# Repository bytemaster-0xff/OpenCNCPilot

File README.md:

# DIY PCB Fab

NOTE: Work in proces, mostly usable but use at your own risk and download updates often.

####Suite of tools for the PCB DIY'er who uses a CNC and/or Laser Cutter to Create Home Brew PCBs

DIY PCB Fab was based off and inspired by the highly successful OpenCNCPilot project by @martin

Key Features

* Open Eagle BRD Files and Generate GCode for Drill and Cutout Milling
* Visualization of Eagle BRD Files 

  [DOCUMENTATION IN PROCESS]

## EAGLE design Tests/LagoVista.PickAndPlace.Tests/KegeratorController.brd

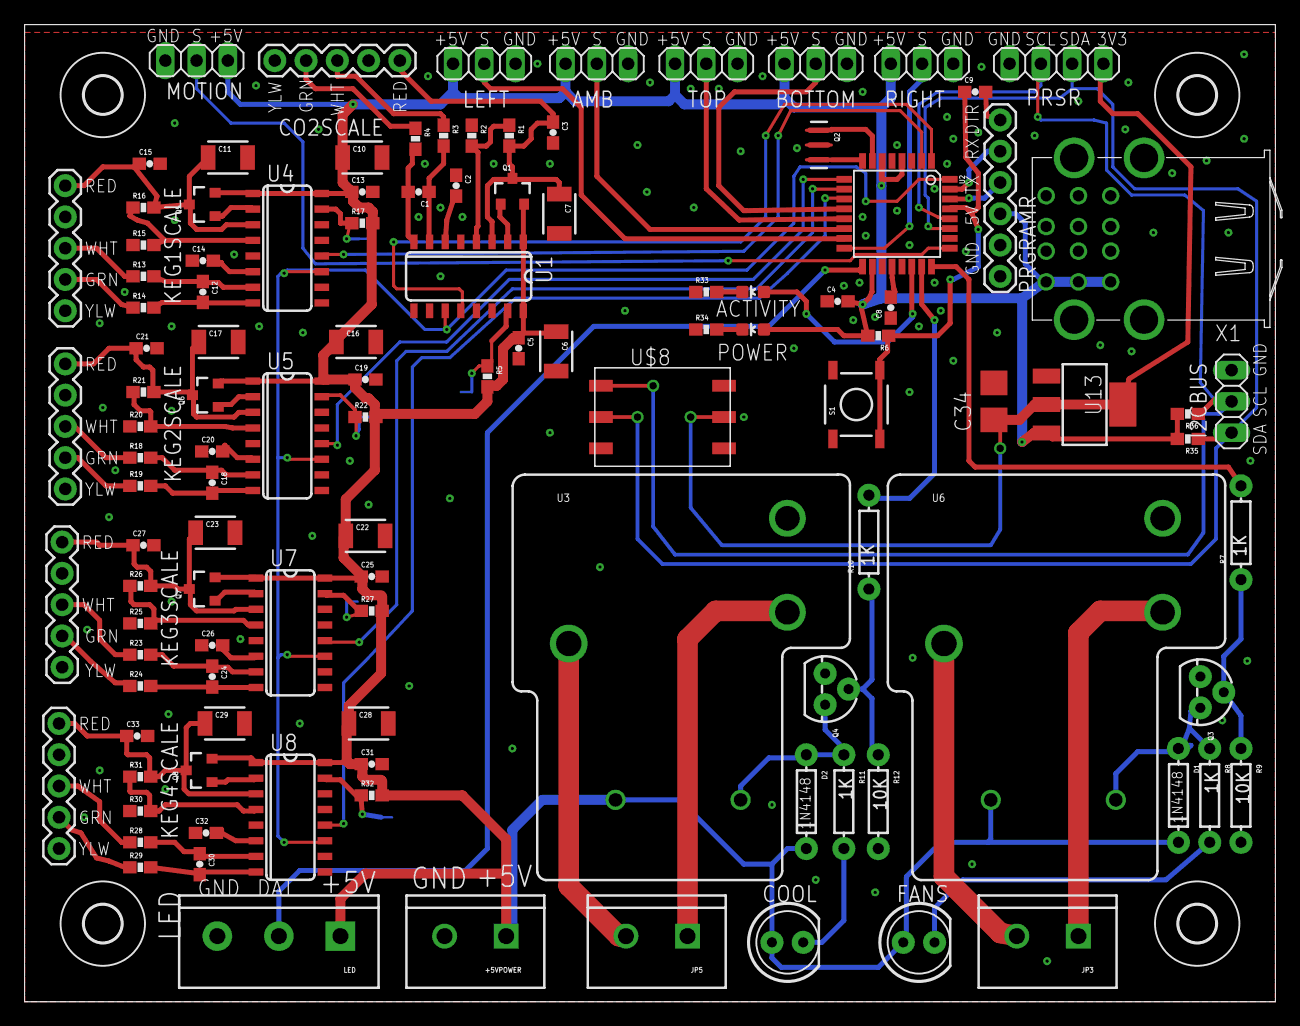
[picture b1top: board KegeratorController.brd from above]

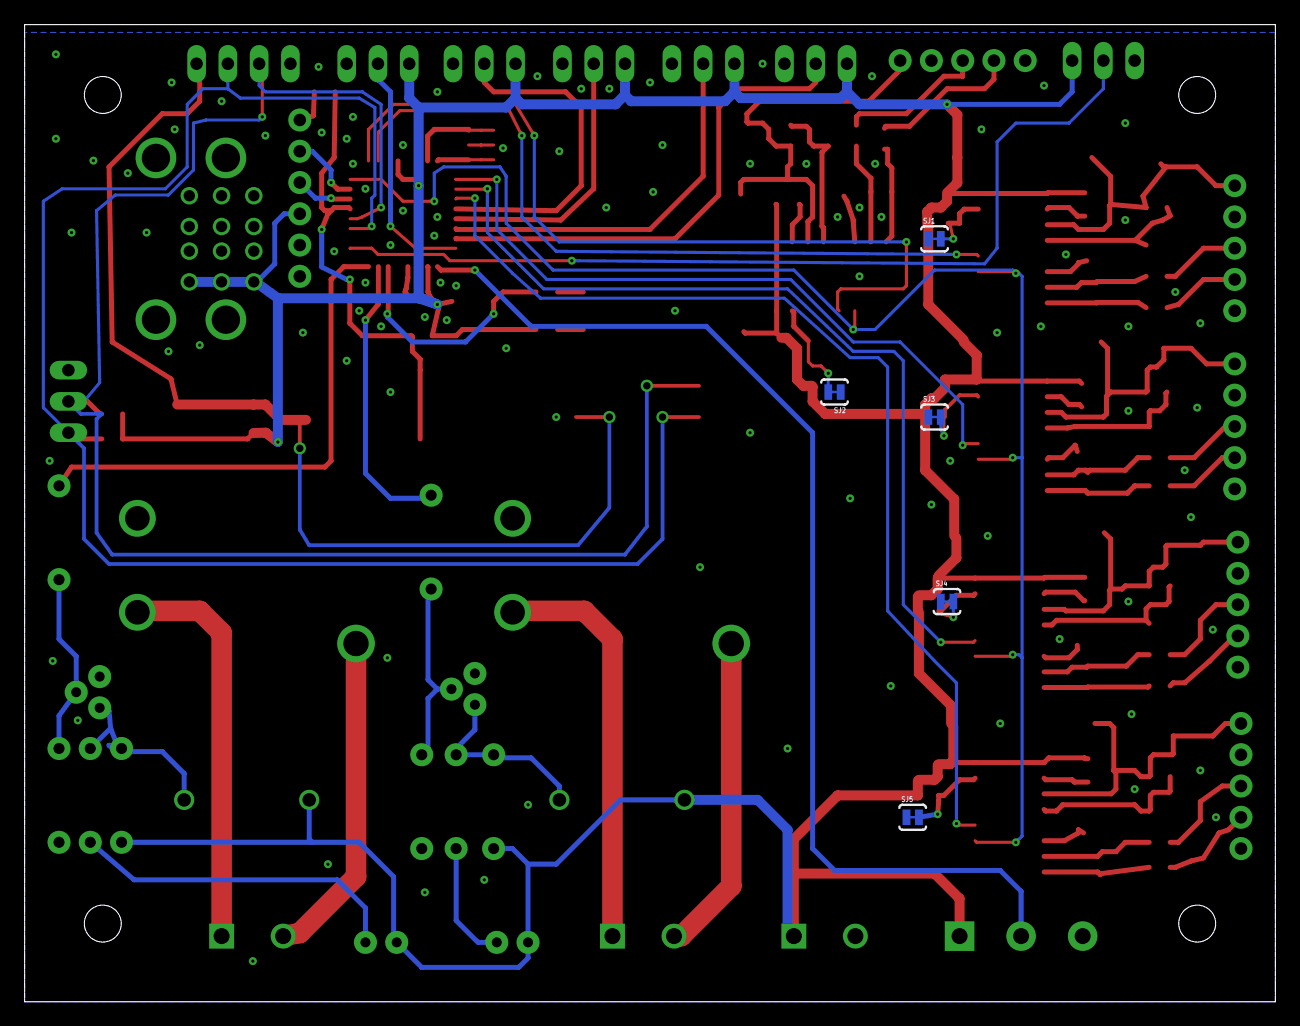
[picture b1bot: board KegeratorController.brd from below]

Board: 2 copper layers, 101.6 x 79.4 mm, 123 parts (5 on the bottom side), 85 nets.

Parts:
+5VPOWER: Load; SCREWTERMINAL-5MM-2
ACTIVITY: Red; 0603-LED-ALT1
AMB: 1X03
BOTTOM: 1X03
C1, C2, C3, C4, C5, C8, C9, C12, C13, C14, C15, C18, C19, C20, C21, C24, C25, C26, C27, C30, C31, C32, C33: 0.1uF; 0603-CAP
C6, C7, C10, C11, C16, C17, C22, C23, C28, C29: 10uF; 1210
C34: 10uF; CT3528
CO2SCALE: 1X05
COOL: LED5MM
D1, D2: 1N4148; DIODE-1N4148
FANS: LED5MM
I2CBUS: 1X03
JP3, JP5: Load; SCREWTERMINAL-5MM-2
KEG1SCALE, KEG2SCALE, KEG3SCALE, KEG4SCALE: 1X05
LED: SCREWTERMINAL-5MM-3
LEFT: 1X03
MOTION: 1X03
POWER: Red; 0603-LED-ALT1
PRGRAMR: FTDI Basic; 1X06
PRSR: 1X04
Q1, Q5, Q6, Q7, Q8: MMBT4403; SOT23-3
Q2: 8/16/20MHz; RESONATOR-SMD-1:1
Q3, Q4: 2N3904; TO-92
R1, R16, R21, R26, R31: 20K; 0603-RES
R2, R15, R20, R25, R30: 8.2K; 0603-RES
R3, R4, R13, R14, R18, R19, R23, R24, R28, R29: 100; 0603-RES
R5, R6, R17, R22, R27, R32, R35, R36: 10K; 0603-RES
R7, R8, R10, R11: 1K; AXIAL-0.3
R9, R12: 10K; AXIAL-0.3
R33, R34: 1K; 0603-RES
RIGHT: 1X03
S1: Reset; TACTILE-SWITCH-SMD-ALT01
SJ1, SJ2, SJ3, SJ4, SJ5: PAD-JUMPER-2-NC_BY_TRACE_YES_SILK
TOP: 1X03
U1, U4, U5, U7, U8: HX711; SO16
U2: ATMEGA328; TQFP32-08
U3, U6: RELAYPTH3; RELAY-T9A-2
U13: LM1117MP-3.3; SOT223
U$4, U$5, U$6, U$7: 3,0
U$8: ABPMANN030PG2A3; SMTAN
X1: USB_3P-85-32003-00X-1; 85-32003-00X-1

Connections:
+3V3: C34.+, PRSR.1, U13.2, U13.4, U$8.P$2
A2+: KEG1SCALE.2, R14.1
A2-: KEG1SCALE.3, R13.1
A3+: KEG2SCALE.2, R19.1
A3-: KEG2SCALE.3, R18.1
A4+: KEG3SCALE.2, R24.1
A4-: KEG3SCALE.3, R23.1
A5+: KEG4SCALE.2, R29.1
A5-: KEG4SCALE.3, R28.1
A+: CO2SCALE.2, R4.1
A-: CO2SCALE.3, R3.1
AREF: C8.2, U2.20
AVDD: C3.1, C7.1, CO2SCALE.5, Q1.3, R1.2, U1.3
AVDD2: C11.1, C15.1, KEG1SCALE.5, Q5.3, R16.2, U4.3
AVDD3: C17.1, C21.1, KEG2SCALE.5, Q6.3, R21.2, U5.3
AVDD4: C23.1, C27.1, KEG3SCALE.5, Q7.3, R26.2, U7.3
AVDD5: C29.1, C33.1, KEG4SCALE.5, Q8.3, R31.2, U8.3
COIL1: D2.A, Q4.3, R11.P$1, U3.COIL2
COIL2: D1.A, Q3.3, R8.P$1, U6.COIL2
COMPRESSOR_RELAY: R10.P$2, U2.23
DAT1: U1.12, U2.1
DAT2: U2.2, U4.12
DAT3: U2.9, U5.12
DAT4: U2.10, U7.12
DAT5: U2.11, U8.12
DHT11-1: LEFT.2, U2.15
DHT11-2: RIGHT.2, U2.16
DHT22-1: BOTTOM.2, U2.12
DHT22-2: TOP.2, U2.13
DHT22-3: AMB.2, U2.14
DTR: C9.2, PRGRAMR.1
GND: +5VPOWER.2, AMB.3, BOTTOM.3, C2.1, C3.2, C4.1, C5.2, C6.2, C7.2, C8.1, C10.2, C11.2, C13.2, C14.1, C15.2, C16.2, C17.2, C19.2, C20.1, C21.2, C22.2, C23.2, C25.2, C26.1, C27.2, C28.2, C29.2, C31.2, C32.1, C33.2, C34.-, CO2SCALE.1, CO2SCALE.4, I2CBUS.3, KEG1SCALE.1, KEG1SCALE.4, KEG2SCALE.1, KEG2SCALE.4, KEG3SCALE.1, KEG3SCALE.4, KEG4SCALE.1, KEG4SCALE.4, LED.3, LEFT.3, MOTION.3, PRGRAMR.5, PRGRAMR.6, PRSR.4, Q2.2, Q3.1, Q4.1, R2.1, R9.P$2, R12.P$2, R15.1, R20.1, R25.1, R30.1, R33.1, R34.1, RIGHT.3, S1.1, S1.2, SJ1.1, SJ2.1, SJ3.1, SJ4.1, SJ5.1, TOP.3, U1.5, U1.14, U2.3, U2.5, U2.21, U4.5, U4.14, U5.5, U5.14, U7.5, U7.14, U8.5, U8.14, U13.1, U$8.P$1, X1.1-4, X1.2-4, X1.3-4
HEAD_FAN_RELAY: R7.P$2, U2.24
I2C-SCL: I2CBUS.2, PRSR.3, R36.1, U2.28, U$8.P$6
I2C-SDA: I2CBUS.1, PRSR.2, R35.1, U2.27, U$8.P$5
LED_OUTPUT: LED.2, U2.17
LED_SIGNAL: ACTIVITY.A, U2.22
MOTION_DETECTOR: MOTION.2, U2.25
unnamed: R5.1, SJ2.2, U1.15
unnamed: C1.1, R3.2, U1.7
unnamed: C1.2, R4.2, U1.8
unnamed: Q1.1, U1.2
unnamed: Q2.3, U2.8
unnamed: R1.1, R2.2, U1.4
unnamed: C2.2, U1.6
unnamed: Q2.1, U2.7
unnamed: Q3.2, R7.P$1, R9.P$1
unnamed: FANS.K, R8.P$2
unnamed: Q4.2, R10.P$1, R12.P$1
unnamed: COOL.K, R11.P$2
unnamed: Q5.1, U4.2
unnamed: R15.2, R16.1, U4.4
unnamed: C14.2, U4.6
unnamed: R17.1, SJ1.2, U4.15
unnamed: C12.1, R13.2, U4.7
unnamed: C12.2, R14.2, U4.8
unnamed: Q6.1, U5.2
unnamed: R20.2, R21.1, U5.4
unnamed: C20.2, U5.6
unnamed: R22.1, SJ3.2, U5.15
unnamed: C18.1, R18.2, U5.7
unnamed: C18.2, R19.2, U5.8
unnamed: Q7.1, U7.2
unnamed: R25.2, R26.1, U7.4
unnamed: C26.2, U7.6
unnamed: R27.1, SJ4.2, U7.15
unnamed: C24.1, R23.2, U7.7
unnamed: C24.2, R24.2, U7.8
unnamed: Q8.1, U8.2
unnamed: R30.2, R31.1, U8.4
unnamed: C32.2, U8.6
unnamed: R32.1, SJ5.2, U8.15
unnamed: C30.1, R28.2, U8.7
unnamed: C30.2, R29.2, U8.8
unnamed: JP3.1, U6.NO
unnamed: JP3.2, U6.MAIN
unnamed: JP5.1, U3.NO
unnamed: JP5.2, U3.MAIN
unnamed: ACTIVITY.C, R33.2
unnamed: POWER.C, R34.2
RESET: C9.1, R6.1, S1.3, S1.4, U2.29
RXI: PRGRAMR.3, U2.30
SCK: U1.11, U2.32, U4.11, U5.11, U7.11, U8.11
TXO: PRGRAMR.2, U2.31
VCC: +5VPOWER.1, AMB.1, BOTTOM.1, C4.2, C5.1, C6.1, C10.1, C13.1, C16.1, C19.1, C22.1, C25.1, C28.1, C31.1, COOL.A, D1.C, D2.C, FANS.A, LED.1, LEFT.1, MOTION.1, POWER.A, PRGRAMR.4, Q1.2, Q5.2, Q6.2, Q7.2, Q8.2, R5.2, R6.2, R17.2, R22.2, R27.2, R32.2, R35.2, R36.2, RIGHT.1, TOP.1, U1.1, U1.16, U2.4, U2.6, U2.18, U3.COIL1, U4.1, U4.16, U5.1, U5.16, U6.COIL1, U7.1, U7.16, U8.1, U8.16, U13.3, X1.1-1, X1.2-1, X1.3-1

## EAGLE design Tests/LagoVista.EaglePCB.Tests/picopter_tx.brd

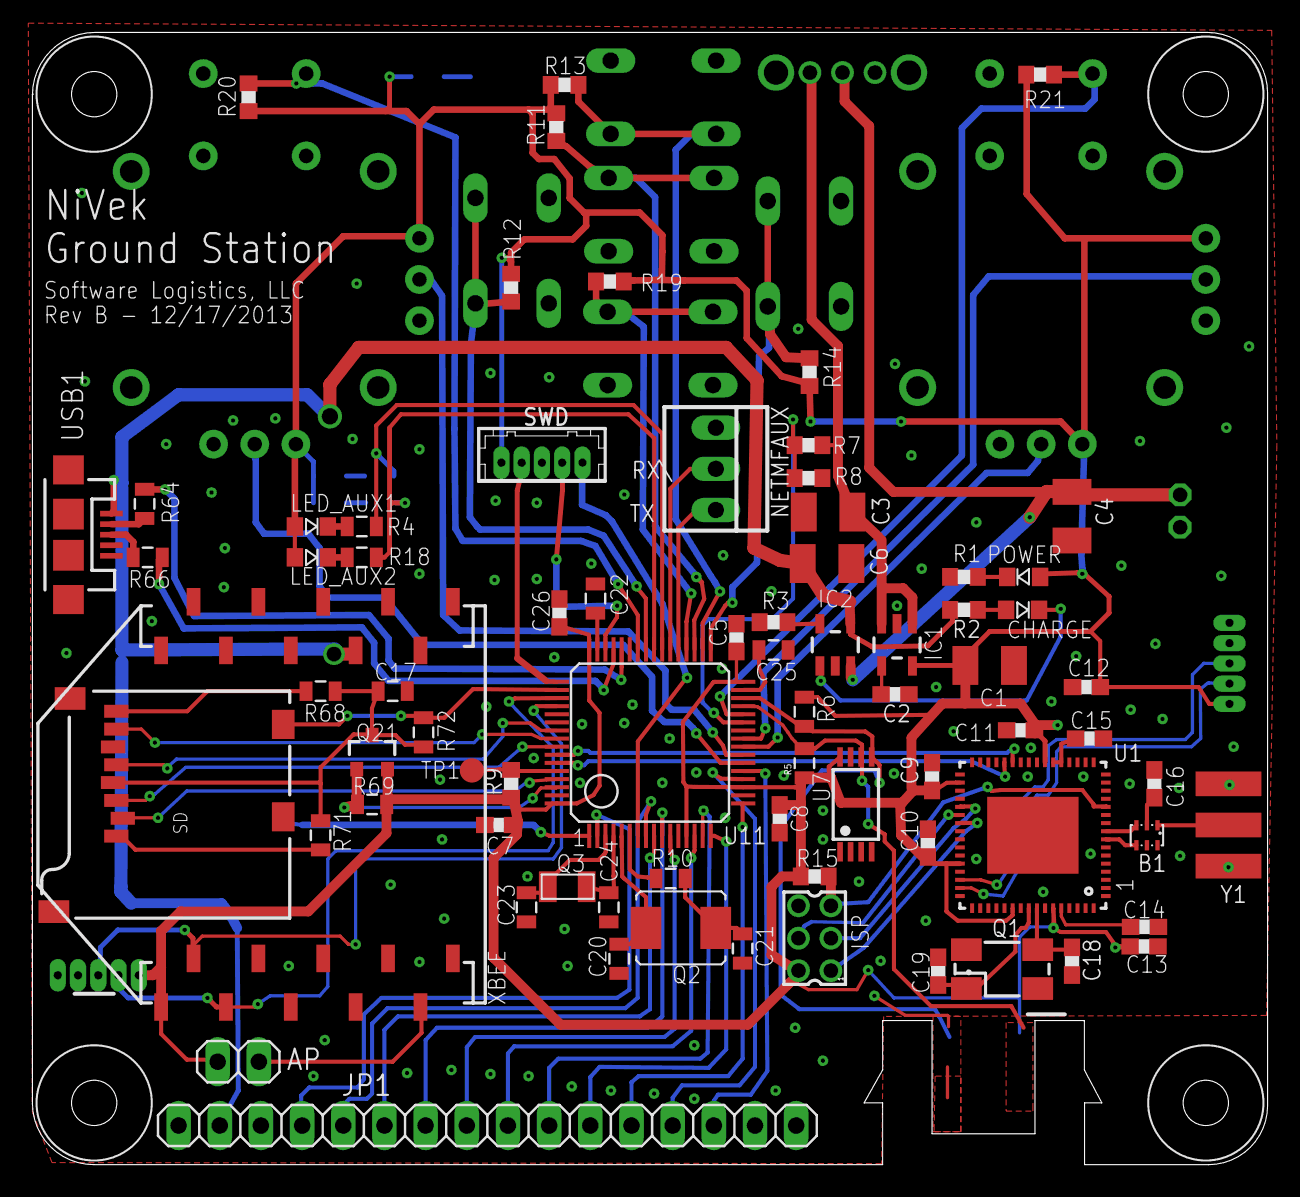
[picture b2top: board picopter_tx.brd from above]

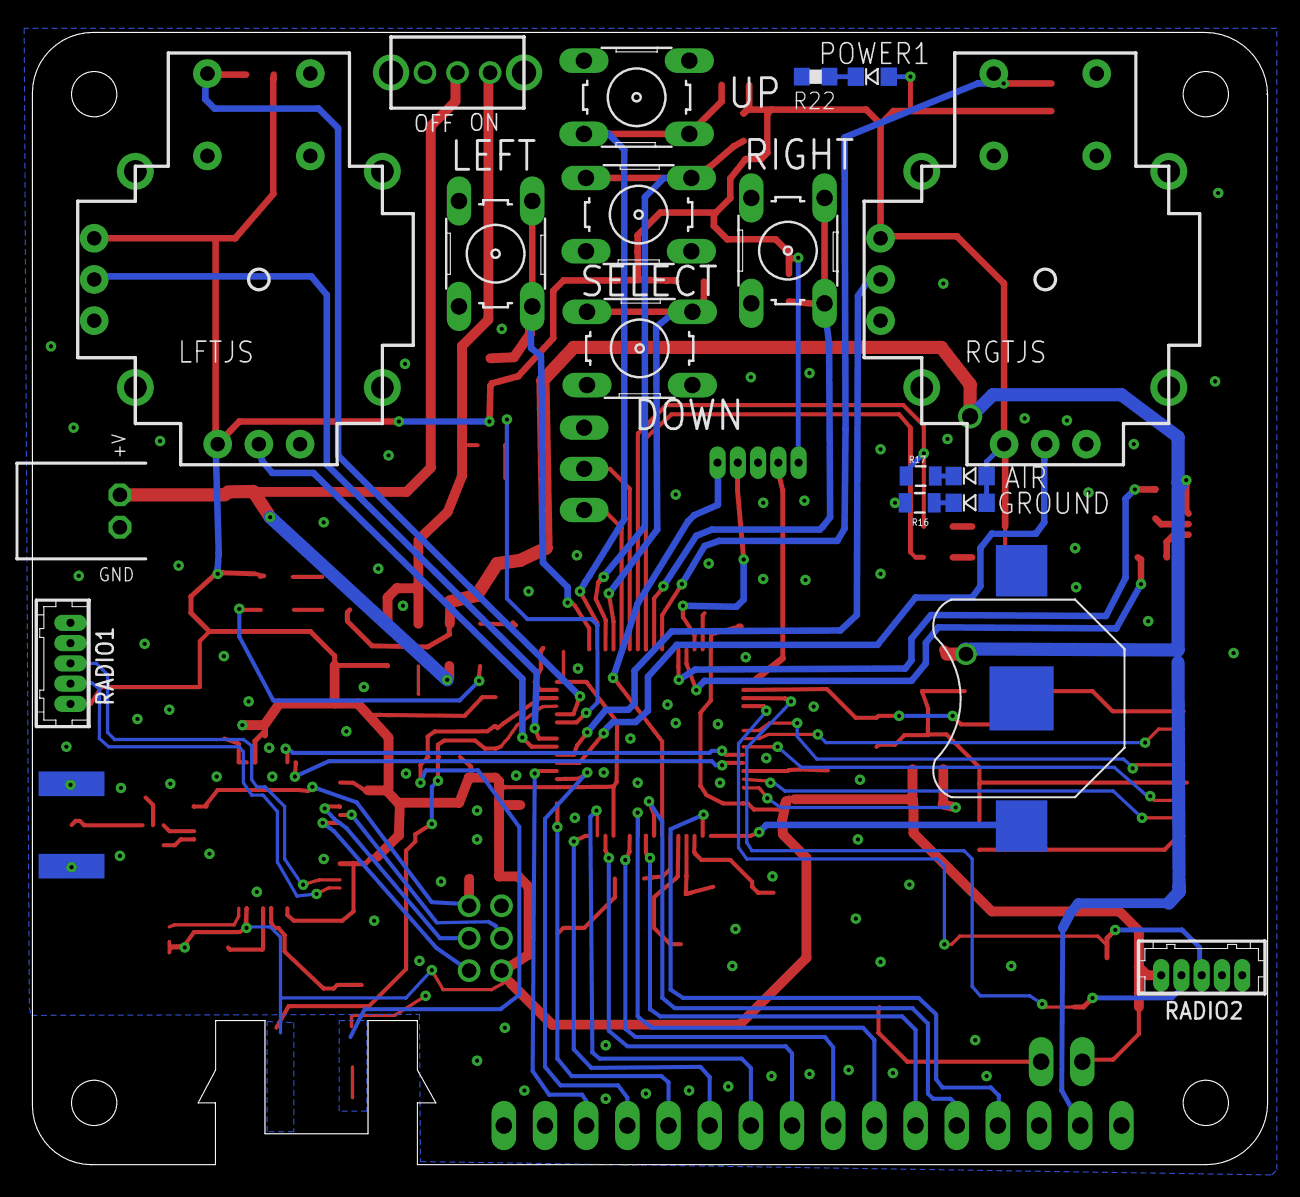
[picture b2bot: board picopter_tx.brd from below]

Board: 2 copper layers, 76.2 x 69.8 mm, 97 parts (18 on the bottom side), 88 nets.

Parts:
AIR: BLUE; LED0805
AP: 1X02
B1: BALUN0805; BALUN
BAT1: BATTCON_12MM
BATT2: BATT-CONNJST-PH-90; JST-PH-2-90
C1: 10uF; SMC_B
C2: 470pF; C0603
C3: 220uF; SMC_B
C4, C6: 4.7uF; SMC_B
C5, C7, C8, C26: 0.1uF; C0603
C9, C10, C11, C12, C13: 0.1uf; C0603
C14, C15: 1uF; C0603
C16: 22pF; C0603
C17: 0.1uF; 0805
C18, C19: 10pF; C0603
C20, C21: 18pf; 0805
C22, C25: 2.2uF; 0805
C23, C24: 6pf; 0805
CHARGE: GREEN; LED0805
DOWN: Reset; B3F-10XX
DRILL1, DRILL2, DRILL3, DRILL4: HOLE-4-40
GROUND: BLUE; LED0805
IC1: Vreg 3V3; SOT23-5
IC2: MCP-LI-CHARGER-1; SOT23-5
ISP: 87758-0616
JP1: 1X16
LED_AUX1, LED_AUX2: BLUE; LED0805
LEFT: Reset; B3F-10XX
LFTJS: JOYSTICKPTH; JOYSTICK
NETMFAUX: 22-23-2031
POWER, POWER1: BLUE; LED0805
Q1: 16MHz; CTS406
Q2: ABRACON_ABM7; ABRACON_ABM7_CERAMIC_XTAL
Q3: XTAL-ECX-31B; CRYSTAL-EXC-31B
Q21: MOSFET-PCHANNELSMD; SOT23-3
R1, R2, R22: 1K; R0603
R3: 3K; R0603
R4, R16, R17, R18: 470; 0805
R5, R68, R69, R71, R72: 10K; 0805
R6: 10k; 0805
R7, R8, R11, R12, R13, R14, R15, R19, R20, R21: 10K; R0603
R9: 4K7; R0603
R10: 390; 0805
R64, R66: 33; 0805
RADIO1, RADIO2: DF13-5P-1.25DSA
RGTJS: JOYSTICKPTH; JOYSTICK
RIGHT: Reset; B3F-10XX
S1: SWITCH-PWR-CNKOS2; SWITCH-SPDT-CNK-OS2
SD: USD-SOCKETNEW; MICRO-SD-SOCKET-PP
SELECT: Reset; B3F-10XX
SWD: DF13-5P-1.25DSA
TP1: TPTP15R; TP15R
U1: ATMEGA128RFA1; QFN-64
U7: 24AA128ST; TSSOP8
U11: STM32F40X; LQFP64
UP: Reset; B3F-10XX
USB1: USB-MICROB
XBEE: XBEE-1B3; XBEE-SMD
Y1: SMA_EDGE; SMA-EDGE

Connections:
!PWR_SD_CTL: Q21.1, R69.1, U11.62
!SD_CS: SD.2, U11.61
!SD_INSERT: R72.1, SD.CD1, U11.50
+3V3: AIR.P$1, AP.1, C1.+, C5.1, C7.1, C8.1, C9.1, C10.1, C11.1, C12.1, C13.1, C26.1, GROUND.P$1, IC1.5, ISP.2, LED_AUX1.P$1, LED_AUX2.P$1, LFTJS.H1, LFTJS.V1, POWER.P$1, POWER1.P$1, Q21.2, R5.1, R6.1, R9.2, R11.1, R12.1, R13.1, R14.1, R15.1, R19.1, R20.1, R21.1, R69.2, RADIO1.1, RADIO2.1, RGTJS.H1, RGTJS.V1, SWD.1, U1.23, U1.34, U1.44, U1.54, U1.59, U7.8, U11.13, U11.19, U11.32, U11.48, U11.64, XBEE.1
+5V: C6.+, IC2.4, JP1.2, R2.1, USB1.VBUS, XBEE.14
AT_CONSOLE_IN: RADIO1.3, U1.46
AT_CONSOLE_OUT: RADIO1.2, U1.47
AT_RESET: ISP.5, R15.2, U1.12
F4_CONSOLE_IN: NETMFAUX.2, U11.38
F4_CONSOLE_OUT: NETMFAUX.3, U11.37
FROM_STM: U1.27, U11.58
GND: B1.5, BAT1.GND, BATT2.N, C1.-, C2.2, C3.-, C4.-, C5.2, C6.-, C7.2, C8.2, C9.2, C10.2, C11.2, C12.2, C13.2, C14.2, C15.2, C16.2, C17.2, C18.2, C19.2, C20.2, C21.2, C22.2, C23.2, C24.2, C25.2, C26.2, DOWN.1, DOWN.2, IC1.2, IC2.2, ISP.6, JP1.1, LEFT.1, LEFT.2, LFTJS.B2A, LFTJS.H3, LFTJS.V3, NETMFAUX.1, R1.1, R3.2, R8.2, R22.1, RADIO1.5, RADIO2.5, RGTJS.B2A, RGTJS.H3, RGTJS.V3, RIGHT.1, RIGHT.2, SD.6, SD.GND1, SD.GND3, SELECT.1, SELECT.2, SWD.3, U1.5, U1.7, U1.10, U1.11, U1.20, U1.24, U1.33, U1.35, U1.45, U1.55, U1.58, U1.61, U1.PAD, U7.1, U7.2, U7.3, U7.4, U7.7, U11.12, U11.18, U11.63, UP.1, UP.2, USB1.GND, USB1.MT1, USB1.MT2, XBEE.10, Y1.GND@0, Y1.GND@1, Y1.GND@2, Y1.GND@3
I2C2_SCL: R5.2, U7.6, U11.29
I2C2_SDA: R6.2, U7.5, U11.30
JSL_HORIZ: LFTJS.H2, U11.24
JSL_VERT: LFTJS.V2, U11.25
JSR_HORIZ: RGTJS.H2, U11.22
JSR_VERT: RGTJS.V2, U11.23
LCD_CS: JP1.6, U11.9
LCD_DAT0: JP1.7, U11.10
LCD_DAT1: JP1.8, U11.11
LCD_DAT2: JP1.9, U11.14
LCD_DAT3: JP1.10, U11.15
LCD_DAT4: JP1.11, U11.16
LCD_DAT5: JP1.12, U11.17
LCD_DAT6: JP1.13, U11.20
LCD_DAT7: JP1.14, U11.21
LCD_RS: JP1.4, U11.2
LCD_RW: JP1.5, U11.8
LED_DRONE: R4.1, R17.1, U11.39
LED_GROUND: R16.1, R18.1, U11.40
MISO: ISP.1, U1.39
MOSI: ISP.4, U1.38
unnamed: CHARGE.C, IC2.1
unnamed: CHARGE.P$1, R2.2
unnamed: AIR.C, R17.2
unnamed: LED_AUX1.C, R4.2
unnamed: POWER.C, R1.2
unnamed: B1.2, C16.1
unnamed: IC2.5, R3.1
unnamed: GROUND.C, R16.2
unnamed: R9.1, TP1.TP, U11.60
unnamed: POWER1.C, R22.2
unnamed: R10.1, U11.6
unnamed: LED_AUX2.C, R18.2
unnamed: C22.1, U11.47
unnamed: C25.1, U11.31
unnamed: C2.1, IC1.4
unnamed: C15.1, U1.21, U1.22
unnamed: C14.1, U1.60
unnamed: B1.1, Y1.SIG
unnamed: B1.3, U1.9
unnamed: B1.4, U1.8
unnamed: C18.1, Q1.3, U1.57
unnamed: C19.1, Q1.1, U1.56
unnamed: R68.2, SD.8
unnamed: R71.2, SD.1
unnamed: R64.1, USB1.D-
unnamed: R66.1, USB1.D+
OSC32_MHZ_IN: C23.1, Q3.P$1, U11.3
OSC32_MHZ_OUT: C24.1, Q3.P$2, U11.4
PWR_SD_CARD: C17.1, Q21.3, R68.1, R71.1, R72.2, SD.4
RESET: SWD.5, U11.7
SCK: ISP.3, U1.37
SD_MISO: SD.7, U11.56
SD_MOSI: SD.3, U11.57
SD_SCK: SD.5, U11.55
SWCLK: SWD.2, U11.49
SWDIO: SWD.4, U11.46
SW_DOWN: DOWN.3, DOWN.4, R19.2, U11.36
SW_JSL: LFTJS.B1A, R21.2, U11.28
SW_JSR: R20.2, RGTJS.B1A, U11.42
SW_LEFT: LEFT.3, LEFT.4, R14.2, U11.33
SW_RIGHT: R12.2, RIGHT.3, RIGHT.4, U11.41
SW_SELECT: R11.2, SELECT.3, SELECT.4, U11.35
SW_UP: R13.2, U11.34, UP.3, UP.4
TO_STM: U1.28, U11.59
USB_DM: R64.2, U11.44
USB_DP: R66.2, U11.45
VBACKBATT: BAT1.PWR@1, U11.1
VBATT: C3.+, IC1.1, IC1.3, R7.1, S1.1
VBATT_ADC: R7.2, R8.1, U11.27
VBATT_IN: BATT2.P, C4.+, IC2.3, S1.2
WIFI_RX: RADIO2.3, U11.52, XBEE.2
WIFI_TX: RADIO2.2, U11.51, XBEE.3
WIFLY_AP: AP.2, XBEE.9
XTAL3: C20.1, Q2.P$1, U11.5
XTAL4: C21.1, Q2.P$2, R10.2

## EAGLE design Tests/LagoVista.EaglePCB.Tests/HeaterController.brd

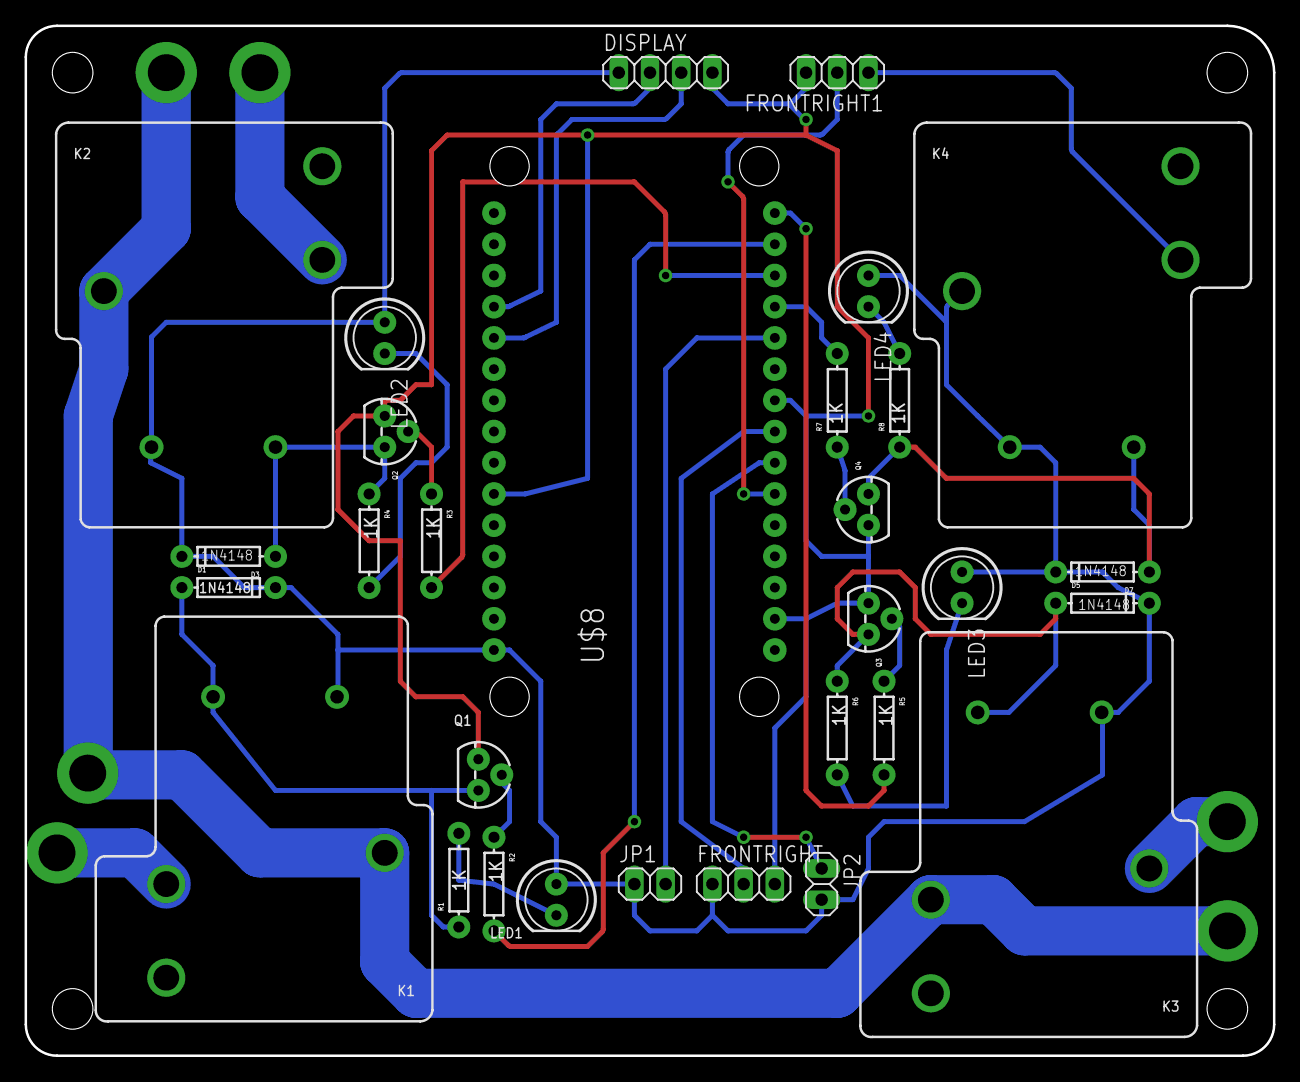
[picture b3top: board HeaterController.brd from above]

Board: 2 copper layers, 101.6 x 83.8 mm, 35 parts (0 on the bottom side), 26 nets.

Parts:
D1, D3, D5, D7: 1N4148; DIODE-1N4148-KIT
DISPLAY: 1X04
FRAME2: FRAME-LETTER; CREATIVE_COMMONS
FRONTRIGHT, FRONTRIGHT1: 1X03
JP1, JP2: 1X02
K1, K2, K3, K4: JQX-15F; RELAY-T90
LED1, LED2, LED3, LED4: LED5MM-KIT
Q1, Q2, Q3, Q4: 2N3904; TO-92-EZ
R1, R2, R3, R4, R5, R6, R7, R8: 1K; AXIAL-0.3EZ
U$3, U$4, U$5, U$7: STAND-OFF
U$8: ESP12E_DEVKIT

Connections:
COIL: D7.A, K4.COIL2, Q4.3, R8.P$1
GND: DISPLAY.4, FRONTRIGHT.3, FRONTRIGHT1.3, Q1.1, Q2.1, Q3.1, Q4.1, U$8.GND@0, U$8.GND@2, U$8.GND@3
HEATER_SW: JP1.2, U$8.D4
LED: FRONTRIGHT1.2, U$8.D7
unnamed: Q2.2, R3.P$1
unnamed: LED2.K, R4.P$2
unnamed: Q3.2, R5.P$1
unnamed: LED3.K, R6.P$2
unnamed: Q4.2, R7.P$1
unnamed: Q1.2, R2.P$1
unnamed: LED4.K, R8.P$2
unnamed: LED1.K, R1.P$2
PRESSURE_SW: JP2.1, U$8.D6
RELAY1_IN: R5.P$2, U$8.D0
RELAY2_IN: R2.P$2, U$8.D1
RELAY3_IN: R3.P$2, U$8.D2
RELAY4_IN: R7.P$2, U$8.D3
RELAY4_NO: FRONTRIGHT1.1, K4.NO
RELAY_C: K1.MAIN, K2.MAIN, K3.NO
SCL: DISPLAY.3, U$8.SD2
SDA: DISPLAY.2, U$8.SD3
SIG_TEMP: FRONTRIGHT.2, U$8.D5
TRIGGER_RELAY1: D5.A, K3.COIL2, Q3.3, R6.P$1
TRIGGER_RELAY2: D1.A, K1.COIL2, Q1.3, R1.P$1
TRIGGER_RELAY3: D3.A, K2.COIL2, Q2.3, R4.P$1
VCC: D1.C, D3.C, D5.C, D7.C, DISPLAY.1, FRONTRIGHT.1, JP1.1, JP2.2, K1.COIL1, K2.COIL1, K3.COIL1, K4.COIL1, K4.MAIN, LED1.A, LED2.A, LED3.A, LED4.A, U$8.VIN

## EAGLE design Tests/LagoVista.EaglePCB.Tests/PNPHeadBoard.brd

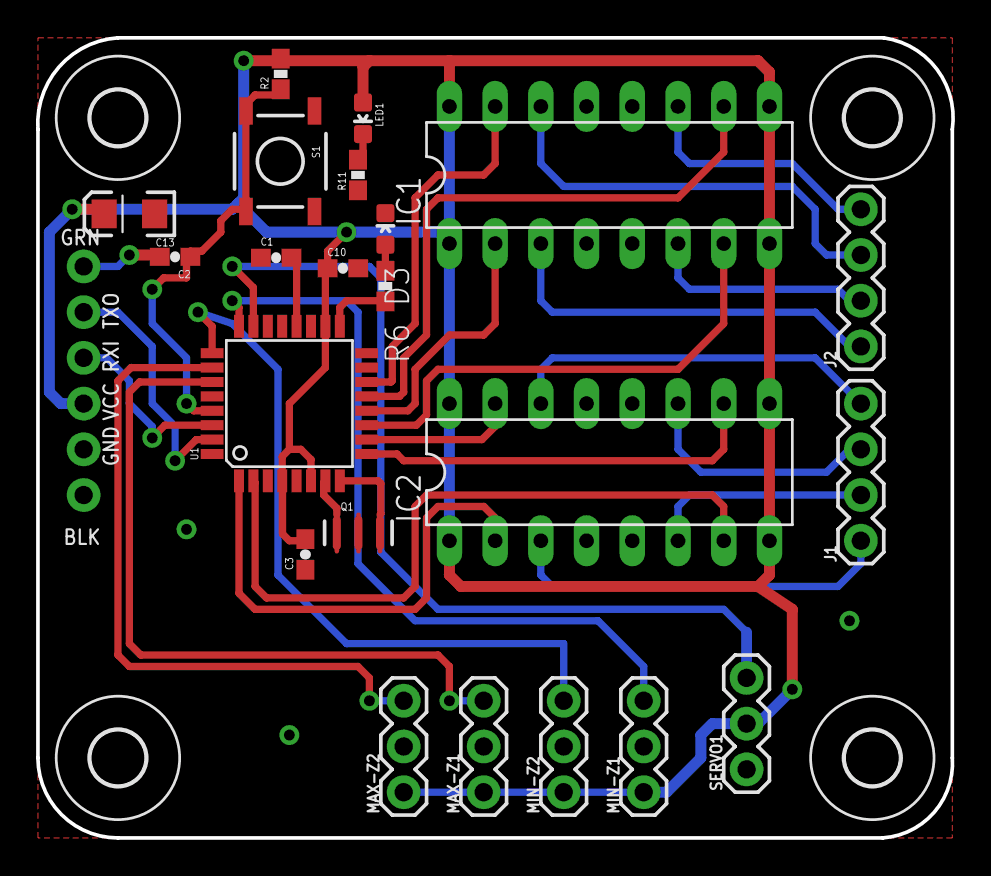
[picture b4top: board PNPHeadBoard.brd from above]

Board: 2 copper layers, 50.8 x 44.5 mm, 27 parts (1 on the bottom side), 33 nets.

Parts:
C1, C2, C3, C10: 0.1uF; 0603-CAP
C13: 10uF; EIA3216
D3: Green; 0603-LED-ALT1
IC1, IC2: L293D; DIL16
J1, J2: 1X04
JP1: FTDI Basic; 1X06
LED1: Red; 0603-LED-ALT1
MAX-Z1, MAX-Z2: 1X03
MIN-Z1, MIN-Z2: 1X03
Q1: 8/16/20MHz; RESONATOR-SMD-1:1
R2, R11: 10K; 0603-RES
R6: 330; 0603-RES
S1: Reset; TACTILE-SWITCH-SMD-ALT01
SERVO1: 1X03
U1: ATMEGA328; TQFP32-08
U$1, U$2, U$4, U$5: 3,0

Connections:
A0: SERVO1.3, U1.23
A1: MIN-Z1.3, U1.24
A2: MIN-Z2.3, U1.25
A3: MAX-Z2.3, U1.26
A4: MAX-Z1.3, U1.27
AREF: C1.2, U1.20
D3: IC2.2, U1.1
D4: IC2.7, U1.2
D5: IC2.10, U1.9
D6: IC2.15, U1.10
D7: IC1.7, U1.11
D8: IC1.2, U1.12
D9: IC1.10, U1.13
D10: IC1.15, U1.14
DTR: C2.2, JP1.1
GND: C1.1, C3.1, C10.2, C13.C, D3.C, IC1.4, IC1.5, IC1.12, IC1.13, IC2.4, IC2.5, IC2.13, JP1.5, JP1.6, MAX-Z1.2, MAX-Z2.2, MIN-Z1.2, MIN-Z2.2, Q1.2, R11.1, S1.1, S1.2, SERVO1.1, U1.3, U1.5, U1.21
unnamed: Q1.3, U1.8
unnamed: Q1.1, U1.7
unnamed: IC2.6, J1.2
unnamed: LED1.C, R11.2
unnamed: IC2.11, J1.3
unnamed: IC2.14, J1.4
unnamed: D3.A, R6.2
unnamed: IC1.14, J2.3
unnamed: IC2.3, J1.1
unnamed: IC1.11, J2.4
unnamed: IC1.6, J2.2
unnamed: IC1.3, J2.1
RESET: C2.1, R2.1, S1.3, S1.4, U1.29
RXI: JP1.3, U1.30
SCK: R6.1, U1.17
TXO: JP1.2, U1.31
VCC: C3.2, C10.1, C13.A, IC1.1, IC1.8, IC1.9, IC1.16, IC2.1, IC2.8, IC2.9, IC2.16, JP1.4, LED1.A, MAX-Z1.1, MAX-Z2.1, MIN-Z1.1, MIN-Z2.1, R2.2, SERVO1.2, U1.4, U1.6, U1.18

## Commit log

2017-01-21 regex compat with SparkFun Stepeko board
2017-01-24 add PLC for core logic
2017-01-24 seems to be working
2017-01-24 progress on converting to MVVM approach
2017-01-25 add preliminary support for computer vision
2017-01-25 working image processing, added XYZ to machine control widget
2017-01-25 progress on machine control panel
2017-01-27 migrate over to LagoVista.WPF support library
2017-01-28 add viewmodels
2017-01-28 wip - ViewModel conversion
2017-01-28 added GCode Machine Simulator
2017-01-28 add marlin support
2017-01-28 start of UI refresh
2017-01-29 set default background color
2017-01-29 more color updates for control bar
2017-01-29 new ui working - mostly
2017-01-29 rename to LagoVista.GCode namespace
2017-01-29 refactor of GCodeParser (mainly to understand how it works)
2017-01-29 get intermediate position of move
2017-01-29 added job processor
2017-01-29 update machine reader
2017-01-29 removed _most_ of CodeBehind code into view models
2017-01-30 wip - need to do a full regression test after refactoring, likely very broken at the moment
2017-01-30 viewmodel refactoring
2017-01-30 added status to GCode Command
2017-01-30 starting to come together - not fully tested
2017-01-31 added binding for NewHightMap
2017-02-01 removed app level variables, all view models are now bidning, close but not there yet
2017-02-01 databindings on NewHeightWindow
2017-02-01 bindings on NewHeightMap and CurrentJob working
2017-02-01 added HeightMapProbing and ToolChange managers
2017-02-01 start cleanup of machine control UI
2017-02-02 vsm and UI cleanup on machine control
2017-02-02 update bindings for MachineControlViewModel
2017-02-03 finish up data binding on stepsize
2017-02-03 better message handling and queue support
2017-02-03 additional settings
2017-02-03 update helix tool kit to only render grid for work surface
2017-02-05 change view
2017-02-05 added code to select camera in settings
2017-02-05 bit of cleanup on Vision Sensor control
2017-02-05 add loading mask for camera startup, has crash bug if switch camera a few times
2017-02-06 early cut on estimating position by job processor
2017-02-06 better estimate of current position of job while running
2017-02-06 additional messaging
2017-02-06 better file handling workaround for binding problem
2017-02-06 image processign
2017-02-07 better buffer handling, replate Task.Wait with SpinWait
2017-02-07 updates to parser
2017-02-07 started work on tool change algorithm
2017-02-10 another major refactor, hopefully last
2017-02-13 fix crash on init
2017-02-13 starting with vision stuff (fun diversion)
2017-02-14 ugly, yet working first cut of fuducial image recog
2017-02-15 added start of PCB editing
2017-02-15 first cut of eagle brd parser
2017-02-15 progress on parsing eagle model
2017-02-15 visualizing pads for SMD from eagle (hard coded for now)
2017-02-16 populate board dim, holes and vias
2017-02-16 Binding to tool path w/ converter
2017-02-16 added binding for heightmap (untested)
2017-02-16 organize managers a bit
2017-02-17 more tweaking of managers
2017-02-17 a bit more cleanup
2017-02-18 added probing, set message output level
2017-02-18 generation of heightmap
2017-02-18 change data structure on heightmap
2017-02-18 progress on heightmap
2017-02-18 height map probing job about done
2017-02-19 height map working on shapeoko :)
2017-02-19 rendering height map gradient in real time
2017-02-19 fix small bug in gcode parser
2017-02-19 prompting for tool change
2017-02-21 added view controls
2017-02-23 updated eagle pcb view
2017-02-24 rendering board outline w/ major hack
2017-02-25 working a bit better with "real" firmware
2017-02-25 usability enhanchements
2017-02-25 working pretty decent w/ GRBL a bit more usability tweaks needed though
2017-02-26 helper icons on job manager
2017-02-26 added better tool change gcode parsing
2017-02-26 convert gcode type to ToolChangeCommand
2017-02-27 start add support, multiple machines
2017-02-28 support for saving multiple machine types
2017-02-28 properly drawing arcs w/ helix
2017-02-28 added spindle and ignore gcode parsing errors for laser
2017-02-28 take into account orientation for image pan view
2017-03-01 zoom in/out now working
2017-03-01 better model positioning, WIP
2017-03-01 add pcb file loading and viewing WIP
2017-03-03 rendering eagle lines
2017-03-04 pcb rendering doesn't suck anymore, about 90% complete
2017-03-04 bit of work with image processing
2017-03-05 seems like tool change is working, need a bit more testing
2017-03-05 added pcb2gcode for reference
2017-03-06 start refactor of machine vision
2017-03-07 added params for machine vision
2017-03-08 parameterize values for machine laearning
2017-03-11 add tool change skip option
2017-03-11 create GCode from board (WIP)
2017-03-11 first cut of edge cutout g-code
2017-03-12 gcode looks good....I think
2017-03-12 added project concept for PCB's
2017-03-12 incorporate project concept and MRUs
2017-03-12 add mru support
2017-03-12 board rendering and project stuff about 80% there
2017-03-12 diversion: full screen machine vision
2017-03-13 fix for CCW arc parsing bug, need to test CW
2017-03-13 render traces as polygons rather than lines
2017-03-13 start processing of wires into traces
2017-03-14 pcb rendering doesn't suck anymore
2017-03-14 start cleanup of machine vision
2017-03-14 add backing stores to vision profile
2017-03-14 add value bindings to machine vision view
2017-03-14 finish wiring up config UI for machine vision
2017-03-15 add eagle pcbgcode integration
2017-03-15 generate gcode for board hold-downs
2017-03-15 bind to new scrap sides/topbottom
2017-03-15 started work on drill rack consolidation
2017-03-15 add feature to consolidate similar tools in tool rack
2017-03-16 first cut of drill rack management complete
2017-03-16 a bit of UI cleanup
2017-03-17 work on height map and etching rendering
2017-03-17 fix bugs in gcode generation
2017-03-17 vision is starting to come alive...has a very long ways to go though
2017-03-18 imaging updates
2017-03-18 machine vision actually starting to work :)
2017-03-18 finding circles and corners!
2017-03-18 add float/int median filters
2017-03-18 add machine controls on vision window
2017-03-18 make sure we use filtered values to display circle mid points
2017-03-19 add visual for board top
2017-03-19 fix bug in rotation logic
2017-03-19 fix some small bugs in eagle parsing/rotation
2017-03-19 first attempt at PCB's miserable failure on both CNC and laser :(
2017-03-19 laser cutter was problem w/ firmware....seemed to etch lines now
2017-03-20 tweaks for laser cutter
2017-03-20 better handling of child windows
2017-03-20 clean up of main window menus WIP
2017-03-22 start adding some tests for gcode processing
2017-03-23 cleanup some unit tests, create method to adjust offsets
2017-03-23 initial support for rotating GCode points
2017-03-24 add gcode command for probe
2017-03-24 updates on height map management
2017-03-24 height map rendering starting to look decent
2017-03-25 change holddown drills to corners
2017-03-25 add frameworks for board alignment
2017-03-25 WIP on board alignment
2017-03-25 initial workflow for board alignment manager
2017-03-25 machine vision should now location position and angle of board
2017-03-26 cleanup drills
2017-03-26 zero z-axis after first height map probe
2017-03-26 add point stabilization filter and tests
2017-03-26 ready for first board alignment machine test :)
2017-03-26 bug fixes on adding PCB to project
2017-03-26 doing board alignment via Machine Vision :) a little fragile yet though
2017-03-26 a bit of tweaking on height map, GCode generation broken :(
2017-03-26 some progress....still a bit to learn
2017-03-27 fixes for genrated GCode
2017-04-07 updates for vision
2017-04-07 fix parser in new marlin response
2017-04-07 updates to machine vision
2017-04-15 various bug fixes...getting close
2017-04-16 add interface to xbox controller
2017-04-16 YAY - Created first PCB, still bugs (I'm sure), but worked great!
2017-04-21 start work on board alignment via machine vision
2017-04-22 more work on PCB positioning
2017-04-22 more nav updates
2017-04-22 tweaks on board layout
2017-04-22 pcb control updates
2017-04-22 switch between camera and tool view working!
2017-04-22 added first cut of x-box controller for machine navigation, also board alignment is very close!
2017-04-23 fix step size setting on MV view model
2017-04-23 fix messaging
2017-04-23 proper rending of new height map, start work on interpolate z tests
2017-04-24 more cleanup
2017-04-27 add LagoVista machine
2017-04-28 add PNP Project
2017-04-28 progress on adding PNP Controls
2017-04-28 bug fixes
2017-04-28 pnp WIP
2017-04-28 board alignment starting to look good!
2017-04-29 add PCB BOM Support
2017-04-30 add PNP Part Package Manager
2017-04-30 add feeder manager
2017-04-30 add class to do board alignment based on angle and machine offset, add test stubs, not working...yet
2017-05-02 add vacuum control
2017-05-06 add socket channel and frameworks for PNP machine
2017-05-06 more updates for DNPNP
2017-05-07 dnpnp progress
2017-05-07 parts for pnp job
2017-05-07 start of managing feeders for a job
2017-05-07 somewhat working on RSPI
2017-05-13 more support for configure PNP job
2017-05-14 machine controllable, issue with endstop
2017-05-14 added visualization for pnp machine
2017-05-14 working better w/ pmp
2017-05-17 refactor of MV classes into base class
2017-05-18 tests on board alignment manager
2017-05-21 get top and bottom cameras working
2017-05-21 homing view seems to be working, tool calibration is close
2017-05-24 update tool calibration UI
2017-05-26 update WinIoT ino file
2017-05-27 more tuning on MV
2017-05-28 job/feeder updates
2017-05-28 more support for feed
2017-05-28 painful progress on MV
2017-05-28 tool alignment seems good
2017-05-28 XAML updates for work alignment
2017-05-28 board alignment work...
2017-05-31 seems to be working well
2017-06-01 minor updates
2017-06-01 progress on PNP setup
2017-06-01 core done for feeder editor
2017-06-03 minor tweaks to MV stuff
2017-06-04 rectangle mv starting to look decent
2017-06-17 now officialy picking and placing
2020-07-18 update repo
2020-07-24 updatates for openplacer
2020-07-25 add fiducial homing
2020-07-28 tool alignment working
2020-07-28 progress on feeders
2020-07-29 calibration looking decent
2020-07-30 progress
2020-07-30 PNP job progress.
2020-07-31 Pick and Place about 25% there
2020-09-10 first successful p&p
2020-09-10 start adding build flavors
2020-09-11 build flavors
2020-09-13 part packs coming together
2020-09-13 progress on part packs
2020-09-14 more part pack management
2020-09-15 setting pp on slots
2020-09-16 WIP part packs
2020-09-19 pnp job mgmt getting close, need a fair amount of cleanup
2020-09-24 add slot and pin navigation
2020-09-24 placer updates
2020-09-25 added new view for machine navigation in a new window
2020-10-10 part-pack locator
2020-10-16 wip repeteir client
2020-10-16 progress on repeteir
2020-10-16 mostly working with repeteir
2020-10-17 ui updates
2020-10-18 progress.....
2020-10-31 convert pnp to gcode job
2020-10-31 getting solid
2020-11-01 remote connection
2020-11-28 close to ready for first place run.
2021-01-22 wip - nozzle alignment
2021-03-07 rotary calibratoin

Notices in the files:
parts and their libraries:
SparkFun-Aesthetics: Licensing: CC v3.0 Share-Alike You are welcome to use this library for commercial purposes.
SparkFun-Aesthetics: Released under the Creative Commons Attribution Share-Alike 4.0 License
SparkFun-Aesthetics: https://creativecommons.org/licenses/by-sa/4.0
